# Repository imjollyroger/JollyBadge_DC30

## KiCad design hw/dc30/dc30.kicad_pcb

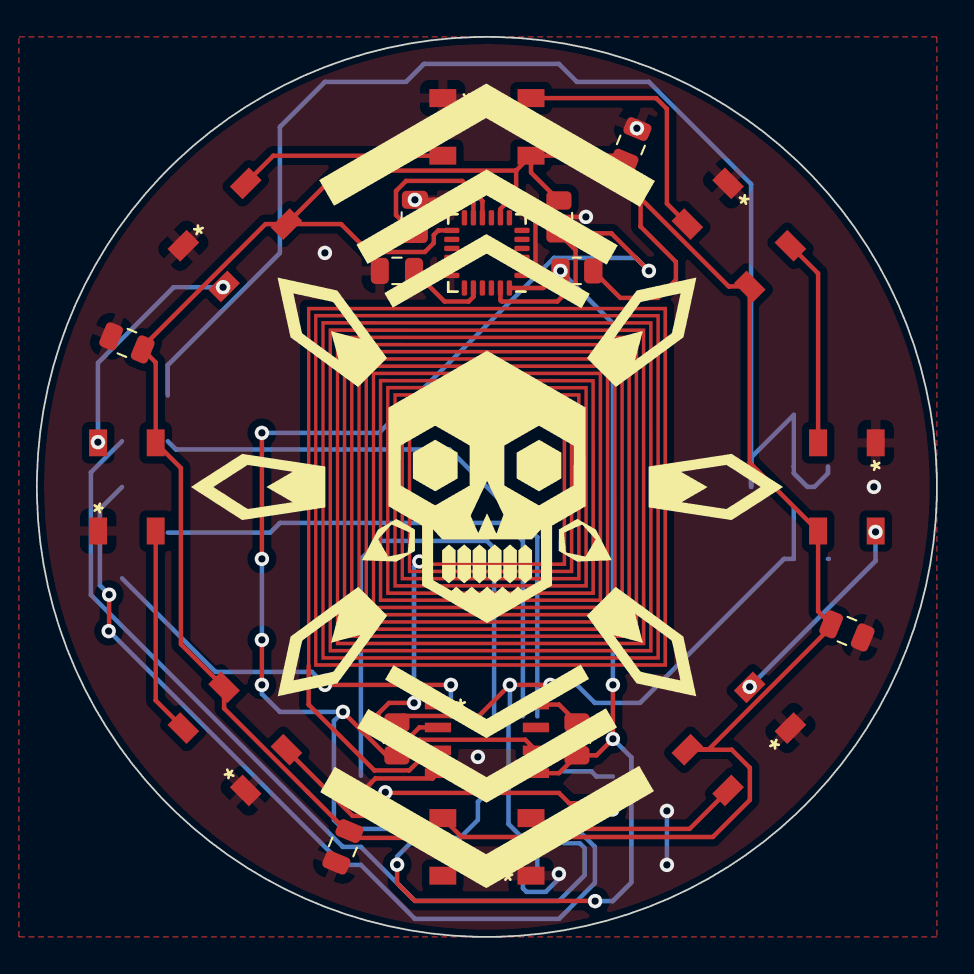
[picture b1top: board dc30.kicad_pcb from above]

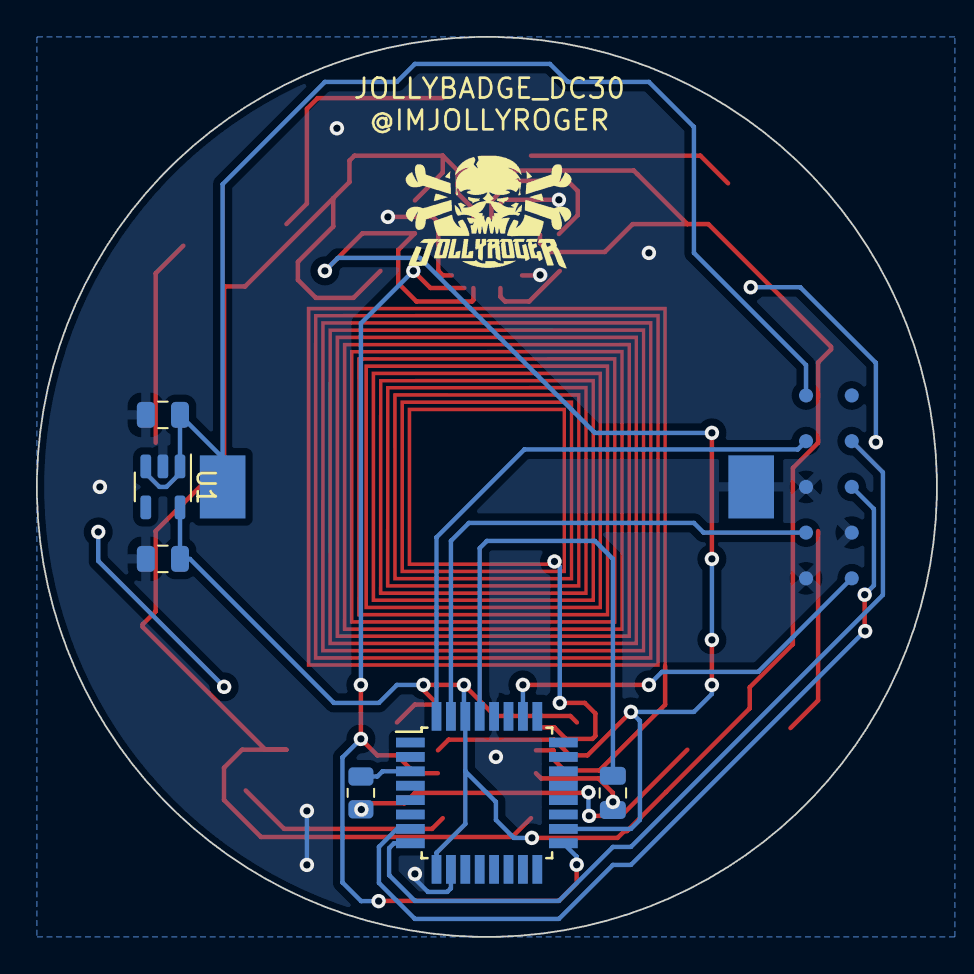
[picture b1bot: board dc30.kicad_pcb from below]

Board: 2 copper layers, 50.0 x 50.0 mm, 29 parts (8 on the bottom side), 21 nets.

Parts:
ANT1: NFC_ANTENNA_20x20; 20x20-rfid-antenna
BAT1: Battery_Cell_2032; BatteryHolder_Keystone_1058_1x2032
C1, C2, C3, C4, C5, C6, C7: 1uF; C_0805_2012Metric
C8: 0.1uF; C_0805_2012Metric
C9: 2.2nF; C_0805_2012Metric
D1, D2, D3, D4, D5, D6, D7, D8: WS2812B; LED_WS2812B_PLCC4_5.0x5.0mm_P3.2mm
JTag1: TC2050-IDC-FP; Tag-Connect_TC2050-IDC-FP_2x05_P1.27mm_Vertical
MPU-6050: MPU-6050; InvenSense_QFN-24_4x4mm_P0.5mm
R1: 470; R_0805_2012Metric
R2, R3, R4, R5: 10K; R_0805_2012Metric
ST25DV1: ST25DV04K-IER6S3
U1: XC6210B332MR; SOT-23-5
U3: ATSAMD21E16A-A; TQFP-32_7x7mm_P0.8mm

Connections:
/NEO_DATA: R1.1, U3.3 (PA02/Analog)
/RESET: JTag1.6, U3.26 (~RESET)
/RX: JTag1.9, U3.8 (PA07/Analog)
/SCL: MPU-6050.23 (SCL), R2.2, R4.2, ST25DV1.6 (SCL), U3.18 (PA17/Digital)
/SDA: MPU-6050.24 (SDA), R3.2, R5.2, ST25DV1.5 (SDA), U3.17 (PA16/Digital)
/SWCLK: JTag1.4, U3.31 (PA30/Digital)
/SWDIO: JTag1.2, U3.32 (PA31/Digital)
/TX: JTag1.8, U3.7 (PA06/Analog)
GND: BAT1.2 (-), C1.2, C2.2, C3.2, C4.2, C5.2, C6.2, C7.2, C8.2, C9.2, D1.3 (VSS), D2.3 (VSS), D3.3 (VSS), D4.3 (VSS), D5.3 (VSS), D6.3 (VSS), D7.3 (VSS), D8.3 (VSS), JTag1.3, JTag1.5, JTag1.7, MPU-6050.1 (CLKIN), MPU-6050.11 (FSYNC), MPU-6050.18 (GND), ST25DV1.4 (VSS), U1.2 (GND), U3.10 (GND), U3.28 (GND)
unnamed: C3.1, U3.29 (VDDCORE)
unnamed: C8.1, MPU-6050.10 (REGOUT)
unnamed: C9.1, MPU-6050.20 (CPOUT)
unnamed: D1.2 (DOUT), D2.4 (DIN)
unnamed: D1.4 (DIN), R1.2
unnamed: D2.2 (DOUT), D3.4 (DIN)
unnamed: D3.2 (DOUT), D4.4 (DIN)
unnamed: D4.2 (DOUT), D5.4 (DIN)
unnamed: D5.2 (DOUT), D6.4 (DIN)
unnamed: D6.2 (DOUT), D7.4 (DIN)
unnamed: D7.2 (DOUT), D8.4 (DIN)
VCC: BAT1.1 (+), C1.1, C2.1, C4.1, C5.1, C6.1, C7.1, D1.1 (VDD), D2.1 (VDD), D3.1 (VDD), D4.1 (VDD), D5.1 (VDD), D6.1 (VDD), D7.1 (VDD), D8.1 (VDD), JTag1.1, MPU-6050.8 (VDDIO), MPU-6050.13 (VDD), R2.1, R3.1, R4.1, R5.1, ST25DV1.8 (VCC), U1.1 (VIN), U1.3 (CE), U1.5 (VOUT), U3.9 (VDDANA), U3.30 (VDDIN)

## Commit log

2022-08-19 JollyBadge DC30 Init Commit

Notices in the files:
parts and their libraries:
Copyright 2021 Accelerated Designs. All rights reserved.
